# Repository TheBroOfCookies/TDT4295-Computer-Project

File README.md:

# TDT4295

Open GuitarZero.kicad_pro in kicad to open the projetc. Then click schematic ceditor to view the schematic. 
Main schematic is empty, except for three other schematics. Namely the PSU schematic, MCU schematic and the FPGA schematic. These files may also be opened directly.
FPGA schematic also contains a schematic for decoupler capacitor circuits.

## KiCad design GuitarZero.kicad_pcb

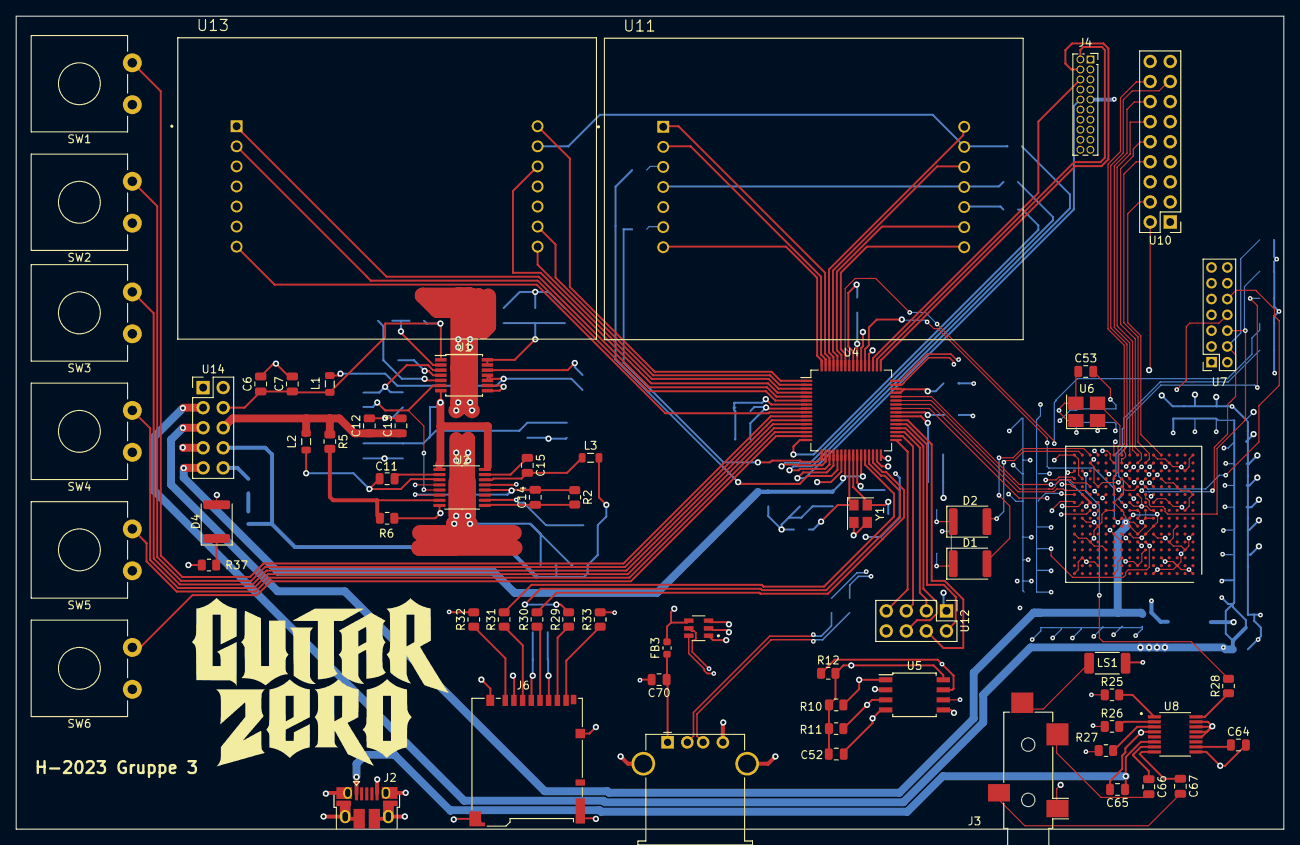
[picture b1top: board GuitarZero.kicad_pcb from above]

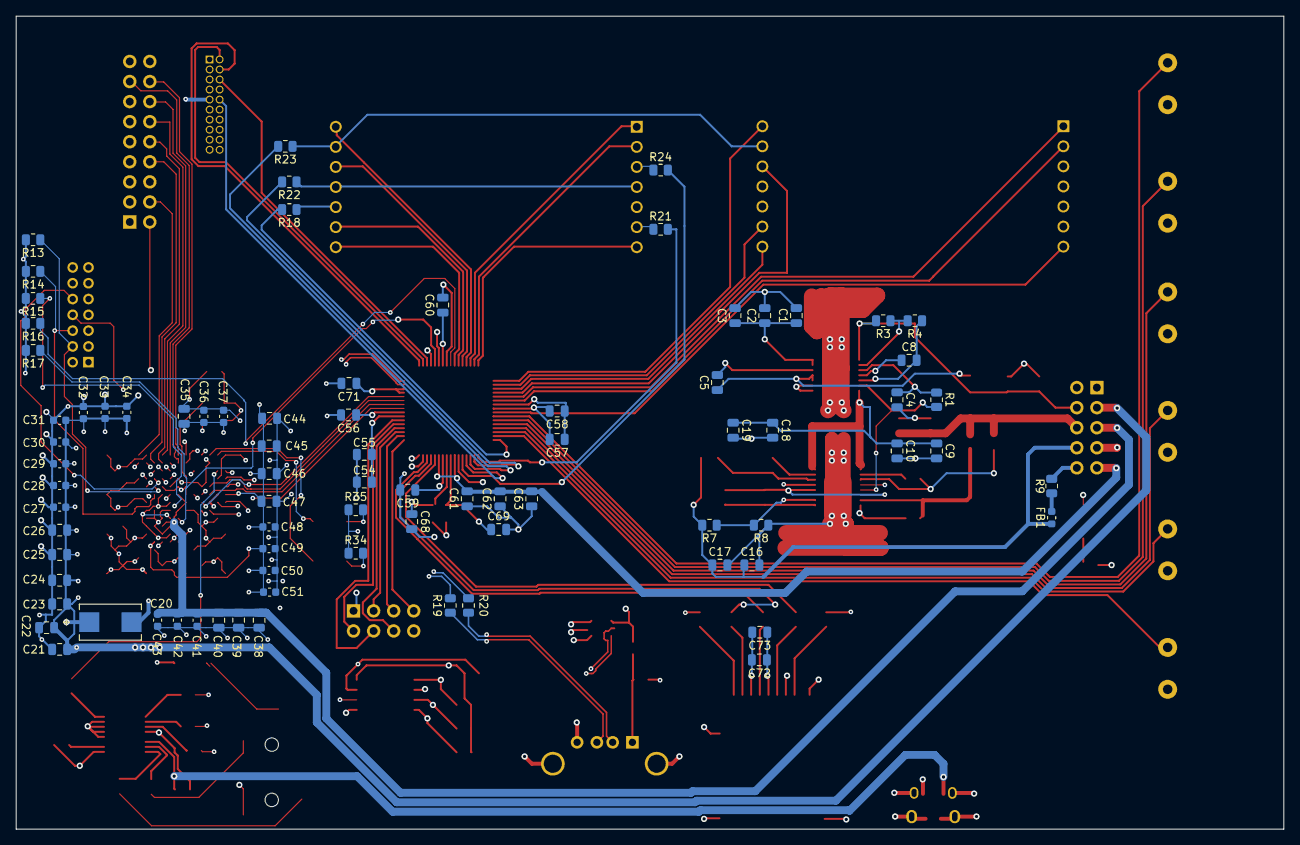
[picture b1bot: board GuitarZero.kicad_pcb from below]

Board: 6 copper layers, 160.4 x 102.9 mm, 145 parts (80 on the bottom side), 138 nets.

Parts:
C1, C9, C18, C54, C58, C61, C64, C65, C66, C67: 10u; C_0805_2012Metric
C2, C5, C10, C11, C15, C19, C52, C53, C55, C57, C59, C60, C72: 100n; C_0805_2012Metric
C3, C35, C70: 100u; C_0805_2012Metric
C4, C14, C56, C71: 1u; C_0805_2012Metric
C6, C7, C12, C13, C16, C17, C73: 22u; C_0805_2012Metric
C8: 3.3n; C_0805_2012Metric
C20: 330u; CAPMP7.6X4.3_1.9N_KEM
C21, C22, C23, C24, C25, C26, C39, C40, C46, C47: 4.7u; C_0805_2012Metric
C27, C28, C29, C30, C31, C32, C33, C34, C36, C37, C41, C42, C43, C48, C49, C50, C51: 0.47u; C_0603_1608Metric
C38, C44, C45: 47u; C_0805_2012Metric
C62, C63, C68, C69: 10n; C_0805_2012Metric
D1, D2, D4: LED; LED_1812_4532Metric
FB1, FB3: FerriteBead; L_0603_1608Metric
H-2023 Gruppe 3: LOGO; Guitar_Zero_Logo
J1: USB_A; USB_A_Stewart_SS-52100-001_Horizontal
J2: USB_B_Micro; USB_Micro-B_Amphenol_10103594-0001LF_Horizontal
J3: AudioJack3_SwitchT; Jack_3.5mm_CUI_SJ-3524-SMT_Horizontal
J4: MCU_Debug; PinSocket_2x10_P1.27mm_Vertical
J6: Micro_SD_Card_Det_Hirose_DM3AT; microSD_HC_Hirose_DM3BT-DSF-PEJS
L1, L2: 1.5u; L_0805_2012Metric
L3: 2.2u; L_0805_2012Metric
LS1: Speaker; R_2010_5025Metric
R1, R2: 100k; R_0805_2012Metric
R3: 6.81k; R_0805_2012Metric
R4, R6, R8: 22.1k; R_0805_2012Metric
R5: 30.1k; R_0805_2012Metric
R7: 73.2k; R_0805_2012Metric
R9: 1; R_0805_2012Metric
R10: 2.4k; R_0805_2012Metric
R11, R12, R15, R16: 4.7k; R_0805_2012Metric
R13, R14: 10k; R_0805_2012Metric
R17, R34, R35, R37: 330; R_0805_2012Metric
R18, R21, R22, R23, R24: 100; R_0805_2012Metric
R19, R20: 15; R_0805_2012Metric
R25, R26, R27, R28, R29, R30, R31: 22; R_0805_2012Metric
R32, R33: 47k; R_0805_2012Metric
SW1, SW2, SW3, SW4, SW5, SW6: SW_Push; SW_CW_GPTS203211B
U1: TPS54325; TSSOP-14-1EP_4.4x5mm_P0.65mm
U2: TSP54294; HTSSOP-16-1EP_4.4x5mm_P0.65mm_EP3x3mm
U3: XC7A100T-FTG256; Xilinx_FTG256
U4: EFM32GG332; TQFP-64_10x10mm_P0.5mm
U5: S25FL127S; SOIC-8W_5.3x5.3mm_P1.27mm
U6: Oscillator; Oscillator_SMD_Abracon_ASE-4Pin_3.2x2.5mm_HandSoldering
U7: FPGA_JTAG_Debug; PinSocket_2x07_P2.00mm_Vertical
U8: PCM1754; SOP63P599X175-16N
U9: TPD_Current_Switch; SOT95P280X145-6N
U10: FPGA_GPIO_Extra; PinHeader_2x09_P2.54mm_Vertical
U11, U13: 5x7 LED_matrix; LED_TA20-11SRWA
U12: MCU_GPIO_Extra; PinHeader_2x04_P2.54mm_Vertical
U14: Power_Jumpers; PinHeader_2x05_P2.54mm_Vertical
Y1: Crystal_GND23; Crystal_SMD_Abracon_ABM8G-4Pin_3.2x2.5mm

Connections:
+1V0: C20.1, C21.1, C22.1, C23.1, C24.1, C25.1, C26.1, C27.1, C28.1, C29.1, C30.1, C31.1, C32.1, C33.1, C34.1, C35.1, C36.1, C37.1, U3.E10 (VCCBRAM), U3.F7 (VCCINT), U3.F9 (VCCINT), U3.F11 (VCCBRAM), U3.G6 (VCCINT), U3.H9 (VCCINT), U3.J6 (VCCINT), U3.K9 (VCCINT), U3.L8 (VCCINT), U14.3 (1V_Out)
+1V8: C38.1, C39.1, C40.1, C41.1, C42.1, C43.1, U3.G8 (VCCADC_0), U3.G10 (VCCAUX), U3.J10 (VCCAUX), U3.K11 (VCCAUX), U3.L10 (VCCAUX), U14.5 (1V8_Out)
+3.3V: C44.1, C45.1, C46.1, C47.1, C48.1, C49.1, C50.1, C51.1, C52.1, C53.1, C54.1, C55.1, C57.1, C58.1, C59.1, C60.1, C71.1, C72.1, C73.1, D4.2 (A), J4.1 (VTARGET), J6.4 (VDD), R10.2, R11.2, R12.2, R13.2, R14.2, R15.2, R16.2, R17.2, R32.2, R33.2, SW1.1, SW2.1, SW3.1, SW4.1, SW5.1, SW6.1, U3.E7 (CFGBVS_0), U3.L6 (VCCO_0), U3.L16 (VCCO_14), U3.M9 (M0_0), U3.M13 (VCCO_14), U3.N10 (VCCO_14), U3.P7 (VCCO_14), U3.R14 (VCCO_14), U3.T11 (VCCO_14), U4.7 (IOVDD_0), U4.26 (IOVDD_3), U4.39 (VDD_DREG), U4.45 (USB_VREGI), U4.46 (USB_VREGO), U4.55 (IOVDD_5), U5.8 (VCC), U6.1 (E/D), U6.4 (VCC), U7.2 (VREF), U10.18 (Vcc), U12.8 (Vcc), U14.7 (3.3V_Out)
+3.3VA: C61.2, C62.2, C63.2, U4.23 (AVDD_1), U4.27 (AVDD_0), U14.9 (3.3VA_Out)
+5V: C1.1, C2.1, C3.1, C9.1, C10.1, C18.1, C19.1, C65.1, J2.1 (VBUS), U1.7 (EN), U1.13 (VIN), U1.14 (VCC), U2.1 (VIN1), U2.16 (VIN2), U8.6 (VCC), U9.3 (IN)
/DAC/BIT_CLOCK: R25.1, U3.P16 (IO_L8N_T1_D12_14)
/DAC/DATA_INN: R26.1, U3.M16 (IO_L7P_T1_D09_14)
/DAC/LEFT_RIGHT_CLOCK: R27.1, U3.N16 (IO_L7N_T1_D10_14)
/DAC/OUT_LEFT: C66.2, J3.T
/DAC/OUT_RIGHT: C67.2, J3.R
/DAC/SYSTEM_CLOCK_INPUT: R28.2, U3.P15 (IO_L8P_T1_D11_14)
/FPGA/Done: R17.1, U3.H10 (DONE_0), U4.53 (PF12)
/FPGA/MCU_SPI_CLCK: U3.L14 (IO_L4P_T0_D04_14), U4.42 (PC9)
/FPGA/MCU_SPI_MISO: U3.K13 (IO_L5P_T0_D06_14), U4.44 (PC11)
/FPGA/MCU_SPI_MOSI: U3.M14 (IO_L4N_T0_D05_14), U4.43 (PC10)
/FPGA/MCU_SPI_Select: U3.L13 (IO_L5N_T0_D07_14), U4.41 (PC8)
/FPGA/program_b: R16.1, U3.L9 (PROGRAM_B_0), U4.57 (PE8)
/MCU/Button 1: SW1.2, U4.10 (PC1)
/MCU/Button 2: SW2.2, U4.11 (PC2)
/MCU/Button 3: SW3.2, U4.12 (PC3)
/MCU/Button 4: SW4.2, U4.13 (PC4)
/MCU/Button 5: SW5.2, U4.14 (PC5)
/MCU/Button 6: SW6.2, U4.15 (PB7)
/MCU/USB_DM: R20.2, U4.47 (PF10)
/MCU/USB_DP: R19.2, U4.48 (PF11)
/MCU/USB_VBUS: FB3.1, U4.52 (USB_VBUS), U9.4 (OUT)
/MCU/USB_VBUSEN: U4.54 (PF5), U9.1 (EN)
/PSU/+1V0: C6.1, C7.1, L1.2, R3.2, U1.1 (VO), U14.4 (1V_In)
/PSU/+1V8: C12.1, C13.1, L2.1, R5.2, U14.6 (1V8_In)
/PSU/+3.3V: C16.1, C17.1, FB1.1, L3.2, R7.2, U14.8 (3.3V_In)
/PSU/+3.3VA: R9.1, U14.10 (3.3VA_In)
GND: C1.2, C2.2, C3.2, C4.2, C6.2, C7.2, C8.2, C9.2, C10.2, C12.2, C13.2, C16.2, C17.2, C18.2, C19.2, C20.2, C21.2, C22.2, C23.2, C24.2, C25.2, C26.2, C27.2, C28.2, C29.2, C30.2, C31.2, C32.2, C33.2, C34.2, C35.2, C36.2, C37.2, C38.2, C39.2, C40.2, C41.2, C42.2, C43.2, C44.2, C45.2, C46.2, C47.2, C48.2, C49.2, C50.2, C51.2, C52.2, C53.2, C54.2, C55.2, C56.2, C57.2, C58.2, C59.2, C60.2, C61.1, C62.1, C63.1, C64.2, C65.2, C68.2, C69.2, C70.2, C71.2, C72.2, C73.2, J1.4 (GND), J1.5 (Shield), J2.5 (GND), J2.6 (Shield), J3.S, J4.3 (GND), J4.5 (GND), J4.9 (CD(GND)), J4.15 (GND), J4.17 (GND), J4.19 (GND), J6.6 (VSS), J6.11 (SHIELD), LS1.1, R4.1, R6.1, R8.1, R34.1, R35.1, R37.1, U1.5 (GND), U1.8 (PGND1), U1.9 (PGND2), U1.15 (PwPd), U2.4 (PGND1), U2.8 (GND), U2.13 (PGND2), U2.17 (PwPd), U3.A1 (GND), U3.A6 (VCCO_35), U3.A11 (GND), U3.A16 (VCCO_15), U3.B3 (VCCO_35), U3.B8 (GND), U3.B13 (VCCO_15), U3.C5 (GND), U3.C10 (VCCO_15), U3.C15 (GND), U3.D2 (GND), U3.D7 (VCCO_35), U3.D12 (GND), U3.E4 (VCCO_35), U3.E9 (GND), U3.E14 (VCCO_15), U3.F1 (VCCO_35), U3.F6 (GND), U3.F8 (VCCBATT_0), U3.F10 (GND), U3.F16 (GND), U3.G3 (GND), U3.G7 (GNDADC_0), U3.G9 (GND), U3.G13 (GND), U3.H6 (GND), U3.H7 (VREFN_0), U3.H8 (VP_0), U3.H15 (VCCO_15), U3.J2 (VCCO_35), U3.J7 (VN_0), U3.J8 (VREFP_0), U3.J9 (GND), U3.J11 (GND), U3.J12 (VCCO_15), U3.K4 (GND), U3.K6 (GND), U3.K14 (GND), U3.L1 (GND), U3.L11 (GND), U3.L15 (IO_L3P_T0_DQS_PUDC_B_14), U3.M3 (VCCO_34), U3.M8 (GND), U3.M10 (M1_0), U3.M11 (M2_0), U3.N5 (GND), U3.N15 (GND), U3.P2 (GND), U3.P12 (GND), U3.R4 (VCCO_34), U3.R9 (GND), U3.T1 (VCCO_34), U3.T6 (GND), U3.T16 (GND), U4.8 (VSS), U4.22 (VSS), U4.56 (VSS), U5.4 (VSS), U6.2 (GND), U7.1 (GND), U7.3 (GND), U7.5 (GND), U7.7 (GND), U7.9 (GND), U7.11 (GND), U7.13 (GND), U8.4 (DGND), U8.9 (AGND), U8.12 (TEST), U8.13 (DEMP), U8.14 (MUTE), U8.15 (FMT), U9.2 (GND), U10.1 (GND), U12.1 (GND), U14.1 (GND), Y1.2, Y1.3
unnamed: D1.2 (A), U3.T14 (IO_L10P_T1_D14_14)
unnamed: D1.1 (K), R34.2
unnamed: D2.2 (A), U3.T15 (IO_L10N_T1_D15_14)
unnamed: D2.1 (K), R35.2
unnamed: D4.1 (K), R37.2
unnamed: FB1.2, R9.2
unnamed: J1.3 (D+), R19.1, U9.6 (D2)
unnamed: J1.2 (D-), R20.1, U9.5 (D1)
unnamed: C70.1, FB3.2, J1.1 (VBUS)
unnamed: J3.TN, LS1.2
unnamed: J4.10 (RESET), U4.20 (RESETn)
unnamed: J4.4 (SWCLK), U4.49 (PF0)
unnamed: J4.2 (SWDIO), U4.50 (PF1)
unnamed: J4.6 (SWO), U4.51 (PF2)
unnamed: J4.8 (TDI), U4.32 (PD4)
unnamed: J6.5 (CLK), R30.1
unnamed: J6.3 (CMD), R31.1
unnamed: J6.7 (DAT0), R29.1
unnamed: J6.8 (DAT1), R33.1
unnamed: J6.1 (DAT2), R32.1
unnamed: J6.2 (DAT3/CD), U4.31 (PD3)
unnamed: R22.1, U11.4 (R3), U11.11 (R3), U13.11 (R3)
unnamed: R1.2, U1.6 (PG), U2.5 (EN1)
unnamed: C8.1, U1.4 (SS)
unnamed: C5.1, L1.1, U1.10 (SW1), U1.11 (SW2)
unnamed: C5.2, U1.12 (VBST)
unnamed: R3.1, R4.2, U1.2 (VFB)
unnamed: C4.1, R1.1, U1.3 (VREG5)
unnamed: C14.2, R2.1, U2.6 (PG1), U2.12 (EN2)
unnamed: C11.2, L2.2, U2.3 (SW1)
unnamed: C15.2, L3.1, U2.14 (SW2)
unnamed: C11.1, U2.2 (VBST1)
unnamed: C15.1, U2.15 (VBST2)
unnamed: R5.1, R6.2, U2.7 (VFB1)
unnamed: R7.1, R8.2, U2.10 (VFB2)
unnamed: C14.1, R2.2, U2.9 (VREG5)
unnamed: U3.J14 (IO_L1N_T0_D01_DIN_14), U5.2 (DQ1)
unnamed: U3.J13 (IO_L1P_T0_D00_MOSI_14), U5.5 (DQ0)
unnamed: R12.1, U3.K16 (IO_L2N_T0_D03_14), U5.7 (HOLD#/DQ3)
unnamed: R11.1, U3.K15 (IO_L2P_T0_D02_14), U5.3 (W#/Vpp/DQ2)
unnamed: R10.1, U3.L12 (IO_L6P_T0_FCS_B_14), U5.1 (S#)
unnamed: U3.N11 (IO_L13P_T2_MRCC_14), U6.3 (OUTPUT)
unnamed: U3.E8 (CCLK_0), U5.6 (C)
unnamed: R15.1, U3.K10 (INIT_B_0)
unnamed: R14.1, U3.L7 (TCK_0), U7.6 (TCK)
unnamed: U3.N7 (TDI_0), U7.10 (TDI)
unnamed: U3.N8 (TDO_0), U7.8 (TDO)
unnamed: R13.1, U3.M7 (TMS_0), U7.4 (TMS)
unnamed: C56.1, U4.40 (DECOUPLE)
unnamed: U4.4 (PA3), U13.12 (C4)
unnamed: R21.2, U4.17 (PA8)
unnamed: R22.2, U4.18 (PA9)
unnamed: R23.2, U4.19 (PA10)
unnamed: R18.2, U4.16 (PB8)
unnamed: R24.2, U4.21 (PB11)
unnamed: C69.1, U4.24 (PB13), Y1.1
unnamed: C68.1, U4.25 (PB14), Y1.4
unnamed: R31.2, U4.28 (PD0)
unnamed: R29.2, U4.29 (PD1)
unnamed: R30.2, U4.30 (PD2)
unnamed: U4.60 (PE11), U11.12 (C4)
unnamed: R25.2, U8.1 (BCK)
unnamed: R26.2, U8.2 (DATA)
unnamed: R27.2, U8.3 (LRCK)
unnamed: R28.1, U8.16 (SCK)
unnamed: C64.1, U8.10 (Vcom)
unnamed: C66.1, U8.7 (VoutL)
unnamed: C67.1, U8.8 (VoutR)
unnamed: U3.P8 (IO_L20P_T3_A08_D24_14), U10.3 (GPIO_1)
unnamed: U3.R5 (IO_L23P_T3_A03_D19_14), U10.2 (GPIO_2)
unnamed: U3.N6 (IO_L19N_T3_A09_D25_VREF_14), U10.5 (GPIO_3)
unnamed: U3.T5 (IO_L23N_T3_A02_D18_14), U10.4 (GPIO_4)
unnamed: U3.M6 (IO_L19P_T3_A10_D26_14), U10.7 (GPIO_5)
unnamed: U3.R6 (IO_L24P_T3_A01_D17_14), U10.6 (GPIO_6)
unnamed: U3.P9 (IO_L18N_T2_A11_D27_14), U10.9 (GPIO_7)
unnamed: U3.R7 (IO_L24N_T3_A00_D16_14), U10.8 (GPIO_8)
unnamed: U3.N9 (IO_L18P_T2_A12_D28_14), U10.11 (GPIO_9)
unnamed: U3.R8 (IO_L20N_T3_A07_D23_14), U10.10 (GPIO_10)
unnamed: U3.R11 (IO_L17N_T2_A13_D29_14), U10.13 (GPIO_11)
unnamed: U3.T8 (IO_L21N_T3_DQS_A06_D22_14), U10.12 (GPIO_12)
unnamed: U3.R10 (IO_L17P_T2_A14_D30_14), U10.15 (GPIO_13)
unnamed: U3.T9 (IO_L22P_T3_A05_D21_14), U10.14 (GPIO_14)
unnamed: U3.T13 (IO_L16N_T2_A15_D31_14), U10.17 (GPIO_15)
unnamed: U3.T10 (IO_L22N_T3_A04_D20_14), U10.16 (GPIO_16)
unnamed: U4.63 (PE14), U11.2 (C1)
unnamed: U4.64 (PE15), U11.7 (C2)
unnamed: U4.62 (PE13), U11.1 (C3)
unnamed: U4.58 (PE9), U11.8 (C5)
unnamed: U4.61 (PE12), U11.14 (C6)
unnamed: U4.59 (PE10), U11.9 (C7)
unnamed: R21.1, U11.6 (R1), U13.6 (R1)
unnamed: R18.1, U11.10 (R2), U13.10 (R2)
unnamed: R24.1, U11.3 (R4), U13.3 (R4)
unnamed: R23.1, U11.13 (R5), U13.13 (R5)
unnamed: U4.35 (PD7), U12.3 (GPIO_1)
unnamed: U4.37 (PC6), U12.2 (GPIO_2)
unnamed: U4.34 (PD6), U12.5 (GPIO_3)
unnamed: U4.38 (PC7), U12.4 (GPIO_4)
unnamed: U4.33 (PD5), U12.7 (GPIO_5)
unnamed: U4.36 (PD8), U12.6 (GPIO_6)
unnamed: U4.6 (PA5), U13.2 (C1)
unnamed: U4.9 (PC0), U13.7 (C2)
unnamed: U4.5 (PA4), U13.1 (C3)
unnamed: U4.3 (PA2), U13.8 (C5)
unnamed: U4.1 (PA0), U13.14 (C6)
unnamed: U4.2 (PA1), U13.9 (C7)

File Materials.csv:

"Id";"Designator";"Footprint";"Quantity";"Designation";"Supplier and ref";
1;"R37,R34,R35,R17";"R_0805_2012Metric";4;"330";;;
2;"D4,D1,D2";"LED_1812_4532Metric";3;"LED";;;
3;"FB3,FB1";"L_0603_1608Metric";2;"FerriteBead";;;
4;"J1";"USB_A_Stewart_SS-52100-001_Horizontal";1;"USB_A";;;
5;"C13,C7,C16,C73,C17,C6,C12";"C_0805_2012Metric";7;"22u";;;
6;"C72,C11,C52,C53,C15,C55,C57,C5,C10,C59,C19,C2,C60";"C_0805_2012Metric";13;"100n";;;
7;"J3";"Jack_3.5mm_CUI_SJ-3524-SMT_Horizontal";1;"AudioJack3_SwitchT";;;
8;"J6";"microSD_HC_Hirose_DM3BT-DSF-PEJS";1;"Micro_SD_Card_Det_Hirose_DM3AT";;;
9;"R29,R30,R27,R26,R25,R31,R28";"R_0805_2012Metric";7;"22";;;
10;"J2";"USB_Micro-B_Amphenol_10103594-0001LF_Horizontal";1;"USB_B_Micro";;;
11;"U14";"PinHeader_2x05_P2.54mm_Vertical";1;"Power_Jumpers";;;
12;"U6";"Oscillator_SMD_Abracon_ASE-4Pin_3.2x2.5mm_HandSoldering";1;"Oscillator";;;
13;"C65,C66,C67,C64,C54,C9,C61,C58,C1,C18";"C_0805_2012Metric";10;"10u";;;
14;"C70,C3,C35";"C_0805_2012Metric";3;"100u";;;
15;"U3";"Xilinx_FTG256";1;"XC7A100T-FTG256";;;
16;"SW3,SW2,SW6,SW5,SW1,SW4";"SW_CW_GPTS203211B";6;"SW_Push";;;
17;"R10";"R_0805_2012Metric";1;"2.4k";;;
18;"U8";"SOP63P599X175-16N";1;"PCM1754";;;
19;"L1,L2";"L_0805_2012Metric";2;"1.5u";;;
20;"J4";"PinHeader_2x10_P2.54mm_Vertical";1;"MCU_Debug";;;
21;"U5";"SOIC-8W_5.3x5.3mm_P1.27mm";1;"S25FL127S";;;
22;"U11,U13";"LED_TA20-11SRWA";2;"5x7 LED_matrix";;;
23;"U4";"TQFP-64_10x10mm_P0.5mm";1;"EFM32GG332";;;
24;"Y1";"Crystal_SMD_Abracon_ABM8G-4Pin_3.2x2.5mm";1;"Crystal_GND23";;;
25;"R2,R1";"R_0805_2012Metric";2;"100k";;;
26;"R7";"R_0805_2012Metric";1;"73.2k";;;
27;"R5";"R_0805_2012Metric";1;"30.1k";;;
28;"R33,R32";"R_0805_2012Metric";2;"47k";;;
29;"R6,R8,R4";"R_0805_2012Metric";3;"22.1k";;;
30;"R19,R20";"R_0805_2012Metric";2;"15";;;
31;"U7";"PinHeader_2x07_P2.54mm_Vertical";1;"FPGA_JTAG_Debug";;;
32;"U9";"SOT95P280X145-6N";1;"TPD_Current_Switch";;;
33;"U2";"HTSSOP-16-1EP_4.4x5mm_P0.65mm_EP3x3mm";1;"TSP54294";;;
34;"LS1";"R_2010_5025Metric";1;"Speaker";;;
35;"C14,C56,C71,C4";"C_0805_2012Metric";4;"1u";;;
36;"R11,R12,R16,R15";"R_0805_2012Metric";4;"4.7k";;;
37;"R9";"R_0805_2012Metric";1;"1";;;
38;"U1";"TSSOP-14-1EP_4.4x5mm_P0.65mm";1;"TPS54325";;;
39;"U10";"PinHeader_2x09_P2.54mm_Vertical";1;"FPGA_GPIO_Extra";;;
40;"L3";"L_0805_2012Metric";1;"2.2u";;;
41;"U12";"PinHeader_2x04_P2.54mm_Vertical";1;"MCU_GPIO_Extra";;;
42;"C31,C37,C30,C36,C51,C41,C34,C32,C33,C50,C42,C43,C29,C27,C49,C48,C28";"C_0805_2012Metric";17;"0.47u";;;
43;"R24,R21,R18,R23,R22";"R_0805_2012Metric";5;"100";;;
44;"R14,R13";"R_0805_2012Metric";2;"10k";;;
45;"R3";"R_0805_2012Metric";1;"6.81k";;;
46;"C24,C40,C23,C26,C47,C25,C22,C46,C21,C39";"C_0805_2012Metric";10;"4.7u";;;
47;"C68,C69,C62,C63";"C_0805_2012Metric";4;"10n";;;
48;"C45,C38,C44";"C_0805_2012Metric";3;"47u";;;
49;"C20";"C_0805_2012Metric";1;"330u";;;
50;"C8";"C_0805_2012Metric";1;"3.3n";;;

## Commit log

2023-09-06 Basic project structure
    Started working on the PSU, which meant adding custom symbols to the symbol table
2023-09-06 Renamed PSU schematic
    Was called PCB which was an unhelpful name
2023-09-06 Finished PSU schematic
    Finish first draft of the PSU schematic. Subject to change
2023-09-06 Fixed wrong capacitor values
    Some capacitor values were wrong, they have now been fixed
2023-09-06 Fixed more wrong values in capacitors and resistors
2023-09-06 Fixed a rule check
    By relabeling some of the custom symbol outputs to passive
2023-09-07 Added FPGA schematic with symbol
    FPGA symbols seem to big to use currently, so they should be resized.
2023-09-07 Update README.md
    Added basic project description
2023-09-07 Fixed typo
2023-09-07 Created .gitignore
2023-09-07 Reformated FPGA
2023-09-07 Resized FPGA schematic page size
2023-09-07 Added MCU schematic
2023-09-10 Changed PSU power pins to hierachical labels
2023-09-10 Added .zip files to .gitignore
    To prevent all backups from being pushed to repository
2023-09-10 Removed some backups
2023-09-10 Added FPGA decoupler capacitors
    Added FPGA_decoup_capacitors.sch file for decoupling circuits
2023-09-11 Added output pins from PSU schematic
    Also renamed FPGA decoupler circuit to not have a typo
2023-09-11 add MCU custom symbol, add symbol to schematic
2023-09-11 Started adding power supply to the FPGA
    Also tried updating .gitignore
2023-09-11 Added SPIFlashPlaceholder symbol
    Until flash is decided, a placeholder has been decided
2023-09-11 Changed spi flash pin info
2023-09-11 Added on chip osillator to FPGA
2023-09-12 Disconnected unused I/O bank in FPGA
2023-09-12 Resized FPGA file down to A3 from A2 to improve readability
2023-09-12 Started on FPGA JTAG Connector
2023-09-12 Connected JTAG debug connector
2023-09-13 Fixed broken oscillator
2023-09-13 Added AudioJack
2023-09-13 Added FPGA to MCU labels
    Setup to communicate via SPI
2023-09-13 Added USB_B_Micro power input
2023-09-13 Wired power supply to digital IO + analog IO + internal decoupler
2023-09-14 Addef outpins for FPGA
2023-09-14 Revert
2023-09-14 Connected MCU and FPGA via SPI
2023-09-14 Added buttons and connected them to the MCU
2023-09-14 Resolved some Electrial Rules
2023-09-14 Fixed overextended wire point
2023-09-14 Changed label to text
2023-09-15 Added DAC schematic
2023-09-15 Changed JACK and Speaker symbol
2023-09-15 Swapped to 3-pin jack with switch
2023-09-15 Added DAC symbol
2023-09-15 Connected FPGA and DAC
2023-09-16 Added MCU Crystal for Clock signal
2023-09-19 Wired FPGA program to MCU
2023-09-19 Added labels in root for USB signals
2023-09-19 Added (mostly) complete USB host wiring on MCU
2023-09-19 Changes GND power pin for PSU components
2023-09-19 Changed AVCC from ferrite bead to 3.3VA
2023-09-19 Connected USB data pins to current switch
2023-09-19 Minor Symbol fix
2023-09-19 Added 16 pins of GPIO backups to FPGA
2023-09-19 add MCU JTAG Debugger
2023-09-20 Reverted USB_A mistakenly deleted
2023-09-20 Fixed power error
2023-09-20 Added LED-s to mcu
2023-09-20 Updated LEDs to match 14 pin layout
2023-09-20 move FPGA_RESET and FPGA_DONE to free US1 pins for SD-card
2023-09-20 add micro SD card
2023-09-20 Added Vcc and GND to FPGA GPIO pinout
2023-09-20 Added final GPIO_pins
2023-09-20 Now follows with Electrical Rules
2023-09-21 Corrected FPGA Debug pin order
2023-09-21 Added PSU jumpers
2023-09-21 Added Anti-noise resistors to DAC
2023-09-21 Added Pullup resistors
    And disconnected unused USB_volt ports
2023-09-21 Disconnected USB_VRGEI/O in root
2023-09-21 Fixed mistake in USB_A connection
2023-09-22 Corrected MCU Debug pin
2023-09-22 Added FPGA debug led
2023-09-22 Fixed PSU Jumper connection
2023-09-22 Made resistor values uniform
2023-09-25 Added footprints to symbols
    Some nice light work
2023-09-25 Started implementing physical layout
2023-09-26 First pass at placing components physically
2023-09-26 Compression of intial placement
2023-09-26 Improved space use for PCB
2023-09-26 Placed components ready for wiring
2023-09-27 Moved some components for better power wiring
2023-09-27 Changed Reistor and Capacitor size fomr 1206 to 0805
2023-09-27 Disconnected unused detect pins for SD card reader
2023-09-27 Added Power LED
2023-09-27 Added Bill of current materials
2023-09-27 Resized Capacitors
2023-09-27 Changed MCU_Debug to 1.27mm pitch
2023-09-27 Changed FPGA_Debug to 2mm pitch and updated PCB
2023-09-27 Made room for PSU heatsinks
2023-09-27 start of psu routing
2023-09-27 Finish Routing of PSU
2023-09-27 Wired MCU in .pcb
2023-09-28 completed DAC
2023-09-28 FPGA - SPI Flash Memory
2023-09-28 Added more track widths
2023-09-28 Added smaller Via diameter
2023-09-28 PCB: Grounded FPGA, wired MCU <-> FPGA
2023-09-28 Finished wiring for most of the FPGA
    GPIO-extra pins remaining
2023-09-28 Fixed 112 design error
    FPGA GPIO pin headers still unrouted
2023-09-28 Moved board cutout to correct layer
2023-09-28 Grouped wires out from fpga to fpga pin header
2023-09-29 Rewired FPGA GPIO out for easier PCB wiring
2023-09-29 FInished wiring FPGA GPIO to pin headers
2023-09-29 Added 3.3V vias for Button 1->6
2023-09-29 Added 1V0 layer, Increased heatsinks
2023-09-29 Differential USB routing, More vias, Connector fix
2023-09-30 Added GuitarZero Logo to PCB and Schematic
2023-09-30 Added names to PCB-design
2023-10-03 Updated BOM
2023-11-22 wrap in folder
